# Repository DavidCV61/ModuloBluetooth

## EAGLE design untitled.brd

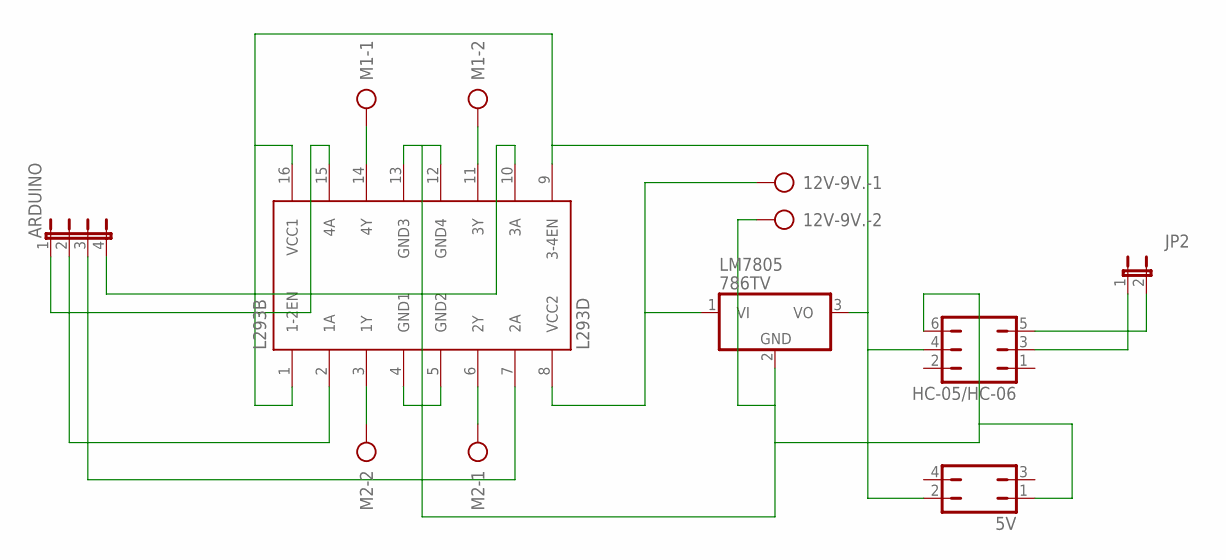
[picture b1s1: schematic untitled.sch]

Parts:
5V: JP2Q; 5V-ARDUINO-OKIOKIS
12V-9V.: AK300/2-OKIS
ARDUINO: JP4E; ARDUINO-2021-0KIS-SI-O-SI
HC-05/HC-06: JP3Q; HC-05-HC-06-OKISOKISS
JP2: JP1E; 2-PINES-OK-2021-TX-RX
L293B: L293D; DIL16
LM7805: 786TV; LM7812/OK
M1, M2: AK300/2-OKIS

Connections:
unnamed: L293B.14 (4Y), M1.1
unnamed: L293B.11 (3Y), M1.2
unnamed: L293B.3 (1Y), M2.2
unnamed: L293B.6 (2Y), M2.1
unnamed: HC-05/HC-06.3, JP2.1
unnamed: 5V.1, 12V-9V..2, HC-05/HC-06.6, L293B.4 (GND1), L293B.5 (GND2), L293B.12 (GND4), L293B.13 (GND3), LM7805.2 (GND)
unnamed: 12V-9V..1, L293B.8 (VCC2), LM7805.1 (VI)
unnamed: HC-05/HC-06.5, JP2.2
unnamed: ARDUINO.2, L293B.2 (1A)
unnamed: ARDUINO.3, L293B.7 (2A)
unnamed: ARDUINO.1, L293B.15 (4A)
unnamed: ARDUINO.4, L293B.10 (3A)
unnamed: 5V.2, HC-05/HC-06.4, L293B.1 (1-2EN), L293B.9 (3-4EN), L293B.16 (VCC1), LM7805.3 (VO)

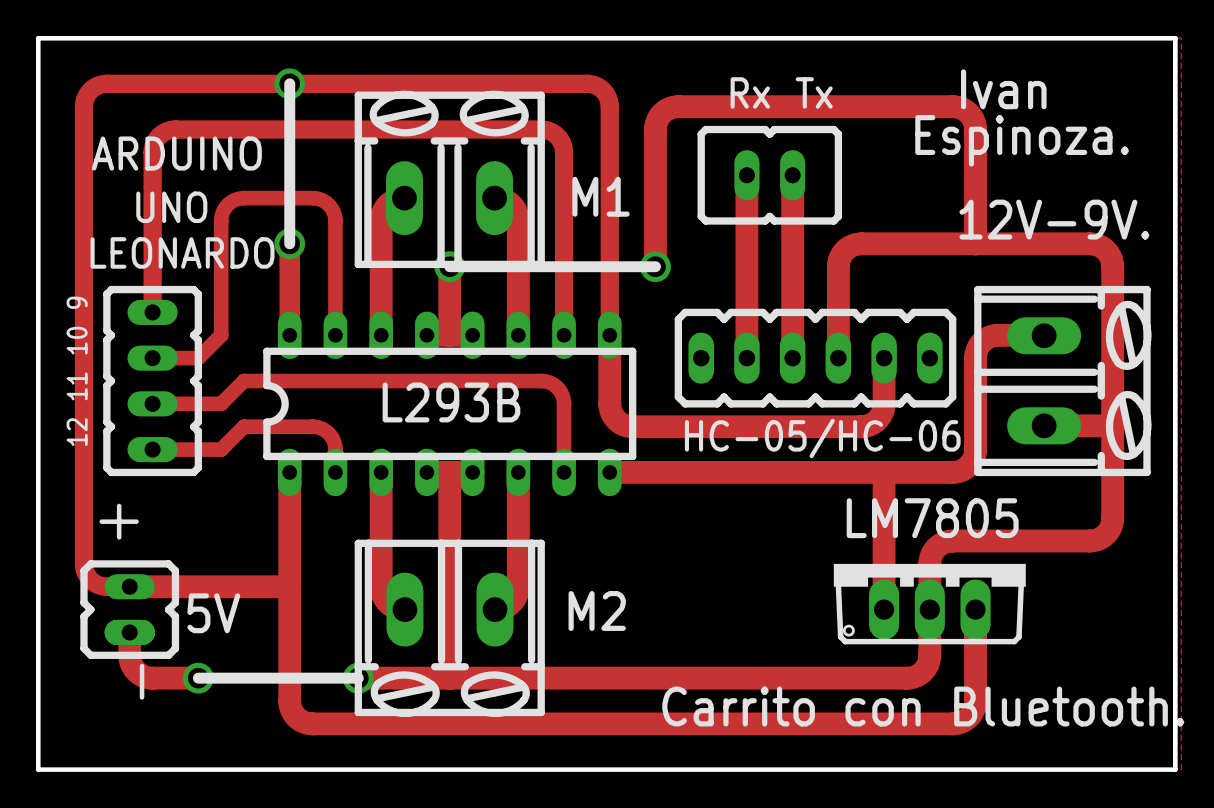
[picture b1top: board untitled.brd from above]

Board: 2 copper layers, 63.2 x 40.6 mm, 9 parts (0 on the bottom side), 13 nets.
